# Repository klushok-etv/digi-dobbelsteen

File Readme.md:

# Digi Dobbelsteen

Digi Dobbelsteen is a digital dice project based on the attiny85 that uses 7 LEDs and a push button.

## Features

- 7 LEDs to display the result of the dice roll
- A push button to roll the dice
- A vibration sensor to roll the dice when the device is shaken

## Usage

The code was written in PlatformIO, so you can use that to compile and upload the code to the attiny85.

The schematic was made in KiCad 7.0, so you can use that to open the schematic and PCB files.

## Schematic

## Charlieplexing

## PCB

## Programing

A precompiled binary is available for the attiny13 under releases. Upload to the chip using the following command:

```console
avrdude -p attiny13 -c usbasp-clone -B 100kHz -e -U flash:w:t13dobbelsteen.elf -U lfuse:w:t13dobbelsteen.elf -U hfuse:w:t13dobbelsteen.elf -U eeprom:w:t13dobbelsteen.elf -U lock:w:t13dobbelsteen.elf
```

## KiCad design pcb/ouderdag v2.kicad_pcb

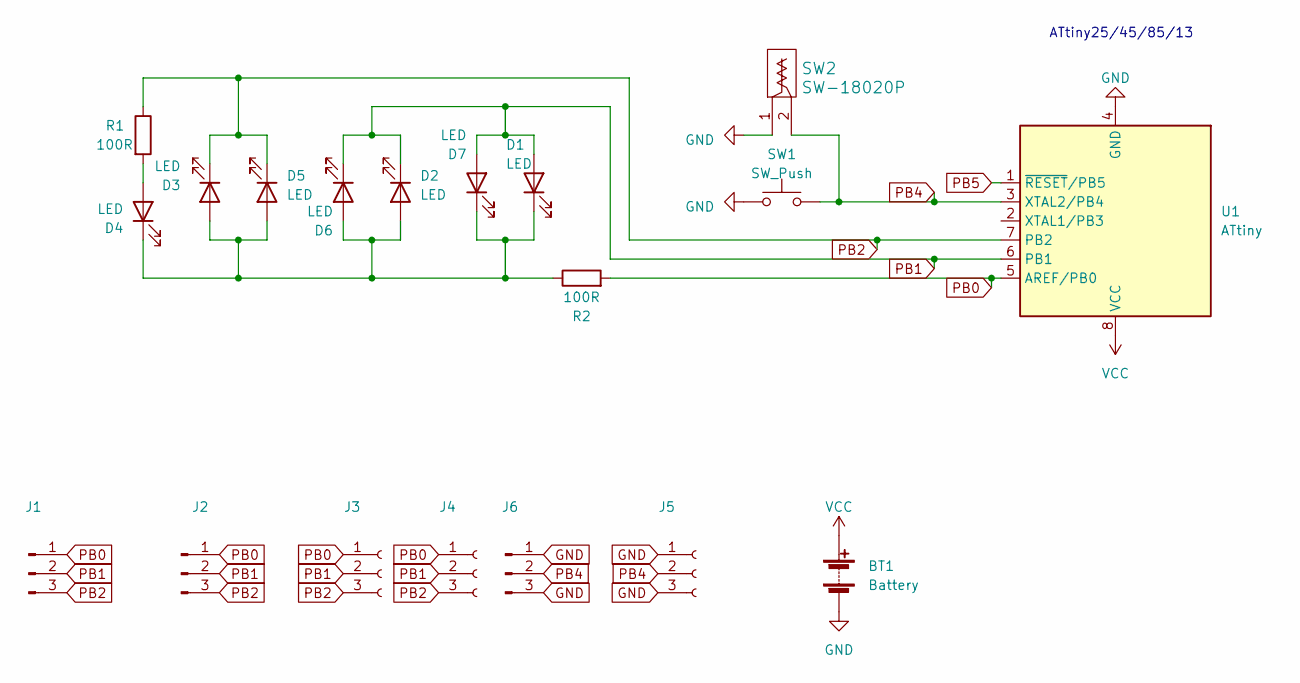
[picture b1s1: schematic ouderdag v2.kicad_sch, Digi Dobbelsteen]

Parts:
BT1: Battery; cr2032
D1, D2, D3, D4, D5, D6, D7: LED; LED_D10.0mm
J1, J2, J6: Conn_01x03_Pin; PinHeader_1x03_P2.54mm_Vertical
J3, J4, J5: Conn_01x03_Socket; PinSocket_1x03_P2.54mm_Vertical
R1, R2: 100R; R_Axial_DIN0207_L6.3mm_D2.5mm_P10.16mm_Horizontal
SW1: SW_Push; SW_PUSH-12mm
SW2: SW-18020P
U1: ATtiny; DIP-8_W7.62mm

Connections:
GND: BT1.2 (-), J5.1, J5.3, J6.1, J6.3, SW1.1, SW2.1, U1.4 (GND)
unnamed: D1.1 (K), D2.2 (A), D3.2 (A), D4.1 (K), D5.2 (A), D6.2 (A), D7.1 (K), R2.1
unnamed: D4.2 (A), R1.2
PB0: J1.1, J2.1, J3.1, J4.1, R2.2, U1.5 (AREF/PB0)
PB1: D1.2 (A), D2.1 (K), D6.1 (K), D7.2 (A), J1.2, J2.2, J3.2, J4.2, U1.6 (PB1)
PB2: D3.1 (K), D5.1 (K), J1.3, J2.3, J3.3, J4.3, R1.1, U1.7 (PB2)
PB4: J5.2, J6.2, SW1.2, SW2.2, U1.3 (XTAL2/PB4)
PB5: U1.1 (~RESET/PB5)
VCC: BT1.1 (+), U1.8 (VCC)

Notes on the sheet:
ATtiny25/45/85/13

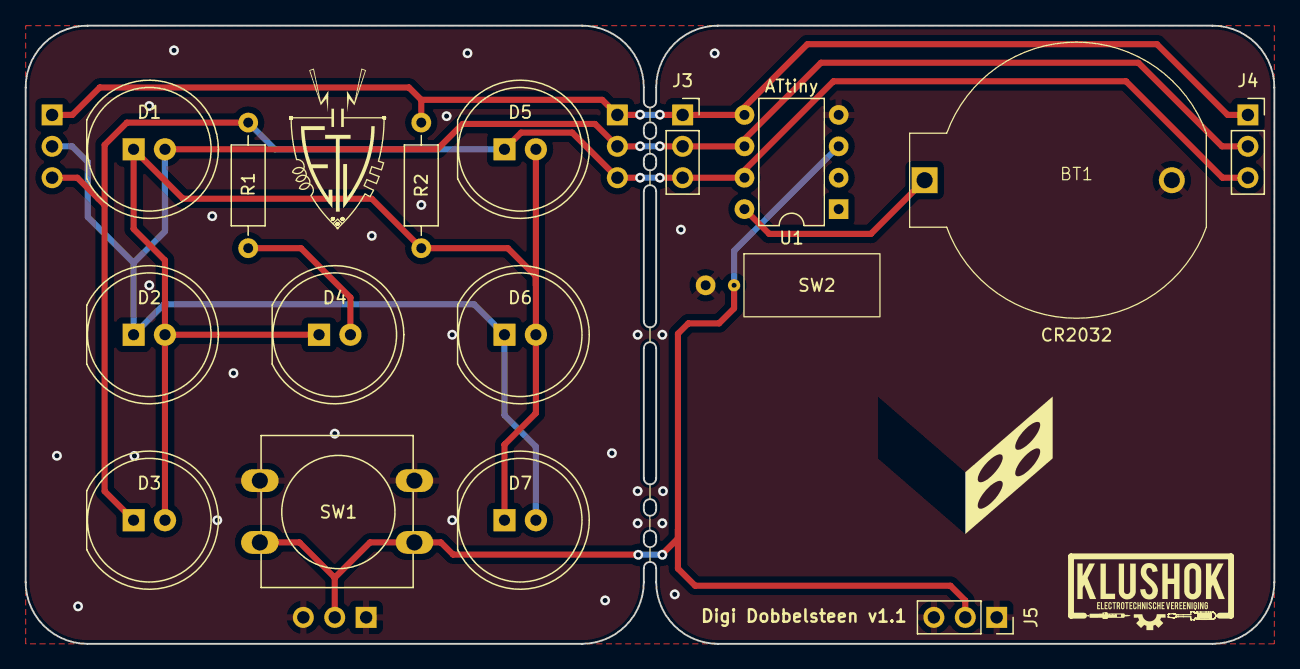
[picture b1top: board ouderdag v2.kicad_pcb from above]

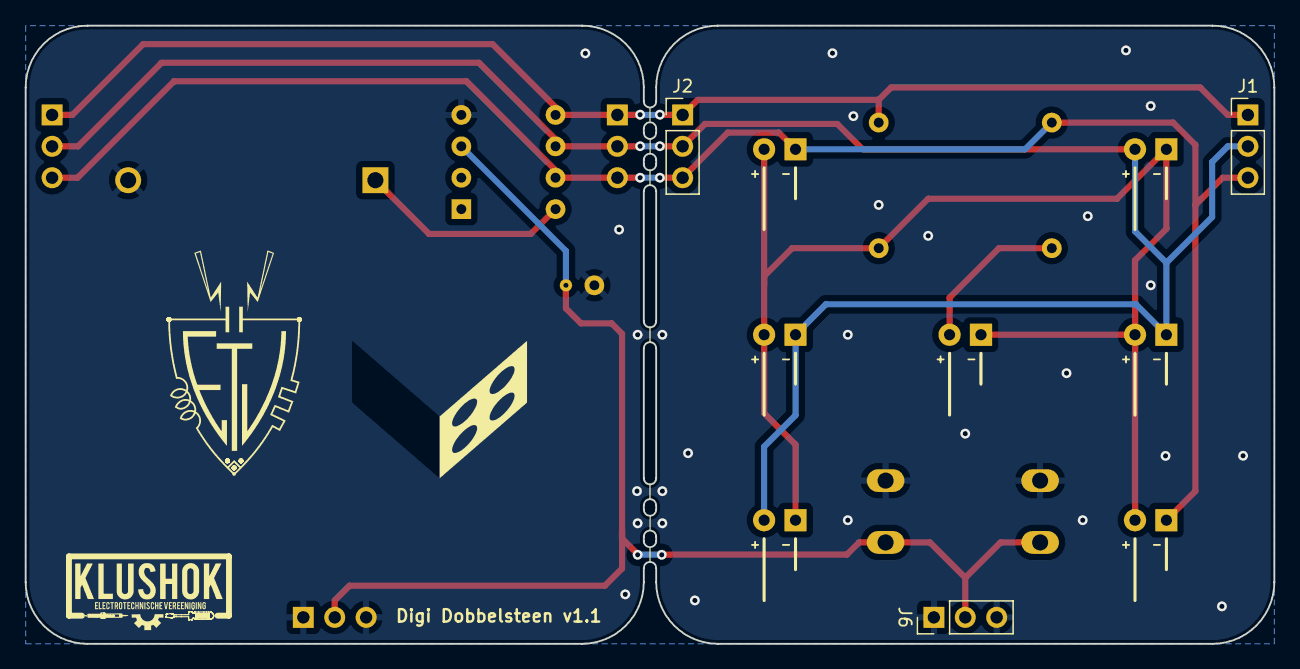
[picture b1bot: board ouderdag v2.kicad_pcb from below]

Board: 2 copper layers, 101.0 x 50.0 mm, 21 parts (4 on the bottom side), 8 nets.

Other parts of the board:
Ref**: Val**; Art
Ref**#2: Val**; Art

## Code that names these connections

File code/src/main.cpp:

/* Attiny Dice v1
  Ryan Kolk - Electrotechnische Vereeniging - 2024
  ATtiny85 @ 8 MHz (internal oscillator; BOD disabled)
   
  CC BY 4.0
  Licensed under a Creative Commons Attribution 4.0 International license: 
  http://creativecommons.org/licenses/by/4.0/

  Atmet Attiny 25/45/85 pinout
                   +-\/-+
  Ain0 (D 5) PB5  1|    |8  Vcc
  Ain3 (D 3) PB3  2|    |7  PB2 (D 2) Ain1
  Ain2 (D 4) PB4  3|    |6  PB1 (D 1) pwm1
             GND  4|    |5  PB0 (D 0) pwm0
                   +----+
*/

#include <Arduino.h>
#include <avr/sleep.h>    // Sleep Modes
#include <avr/power.h>    // Power management

void goToSleep ();

int animateRolling();
void nonBlockingDelay(int ms);
void flashNumber(int num);
void displayNumber(int num);
//Initial brightness levels for the rows
bool Level[4] = {0,0,0,0};
const uint8_t animation[4] = {1,2,3,2};

//Matrix to map numbers 1-6 to the correct leds
const bool Number[6][4] = {
  {1,0,0,0},
  {0,1,0,0},
  {1,1,0,0},
  {0,1,0,1},
  {1,1,0,1},
  {0,1,1,1},
};
bool interrupt = false;
bool awake = true;
static uint8_t row, ramp;
void(* resetFunc) (void) = 0;

ISR (PCINT0_vect)        // Interrupt service routine 
{
  MCUCR&=~(1<<SE);      //Disabling sleep mode inside interrupt routine
  if(awake && digitalRead(PB4) == LOW){
    // resetFunc();
    interrupt=true;
  }
}


// Timer overflow interrupt
ISR(TIM1_COMPA_vect) {
  static uint8_t dir, out;
    row = (row + 1) & 0x03;
    if(row == 0){
      dir=0b101;
      out=0b100;
    } else if(row == 1){
      dir=0b101;
      out=0b001;
    } else if(row == 2){
      dir=0b011;
      out=0b001;
    } else if(row == 3){
      dir=0b011;
      out=0b010;
    }
  if (Level[row] == 0){            // Turn off LED if brightness is 0
    out = 0b000;
    dir=0b000;
  }
  
  DDRB = (DDRB & 0xF8) | dir;         // Set Pin direction. 1 is output, 0 is input (High impedance)
  PORTB = (PORTB & 0xF8) | out;       // Set Pin. 1 is high, 0 is low
}

void setup() {
  if(F_CPU == 8000000) clock_prescale_set(clock_div_1); // Set clock to 8MHz

  // Set up Timer/Counter1 to contol the LEDs
  TCCR1 = 1<<CTC1 | 1<<CS10;          // Divide by 2
  GTCCR = 0;                          // No PWM
  OCR1A = 0;
  OCR1C = 125-1;                      // 16kHz
  TIMSK = TIMSK | 1<<OCIE1A;          // Compare Match A interrupt

  //Setup sleep with interrupt on PB4
  pinMode (PB4, INPUT);     
  digitalWrite (PB4, HIGH);           // Set internal pullup
  PCMSK  |= bit (PCINT4);             // interrupt on PB4
  GIFR   |= bit (PCIF);               // Clear any outstanding interrupts
  GIMSK  |= bit (PCIE);               // Enable pin change interrupts 
  GIMSK |= (1 << PCIE);
  int randomness = analogRead(PB3);// Get a bit of randomness from analog pin that is not being used
  randomSeed(randomness);    // Set seed for the random number generator
}
void loop () {
  int number = animateRolling();

  delay(300);
  flashNumber(number);
  interrupt=false;
  nonBlockingDelay(1500);
  if(interrupt){
    interrupt = false;
    return;
  }
  goToSleep();
  
}

int animateRolling(){
  int randomNumber = 0;
  int length = random(6,15);
  for(int i=0; i<length; i++){
    randomNumber = random(0,6);
    displayNumber(randomNumber);
    nonBlockingDelay(50 + (i * 350 / length));
    if(interrupt){
      length = random(6,15);
      i=0;
      interrupt = false;
      delay(50);
    }
  }
  return randomNumber;
}

void nonBlockingDelay(int ms) {
  for(int i=0; i<ms; i++){
    delay(1);
    if(interrupt)
     return;
  }
  return;
}

void flashNumber(int num){
  for(int i=0; i<2; i++){
    displayNumber(num);
    delay(400);

    displayNumber(-1);
    delay(400);
  }
  displayNumber(num);
}

void displayNumber(int num){
  if(num == -1){
    for(int i=0; i<4; i++){
      Level[i] = 0;
    }
  } else {
    for(int i=0; i<4; i++){
      Level[i] = Number[num][i];
    }
  }
  
}

void goToSleep () {
  for(int i=0; i<4; i++){
    Level[i] = 0;
  }
  MCUCR|=(1<<SM1);      // Enabling sleep mode and powerdown sleep mode
  MCUCR|= (1<<SE);     //Enabling sleep enable bit
  DDRB = (DDRB & 0xF8) | 0b000;
  PORTB = (PORTB & 0xF8) | 0b000;
  delay(10);
  ramp=0;
  row=0;
  awake = false;
  backtosleep: 
  set_sleep_mode(SLEEP_MODE_PWR_DOWN);
  ADCSRA = 0;                         // turn off ADC
  power_all_disable ();               // power off ADC, Timer 0 and 1, serial interface
  sleep_enable();
  sei();  
  sleep_cpu();   
  cli();                            
  sleep_disable();  
  sei();       
  power_all_enable();                 // power everything back on
  if(digitalRead(PB4) == HIGH){
    goto backtosleep;
  }
  awake = true;
}

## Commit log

2024-02-13 added start on manual
2024-03-22 updated code and pcb
2024-03-22 Update semiautomatic.sh
    Fix input queue issue
2024-03-23 cleanup repo
2025-03-27 change to generic ATtiny
    PCB changes:
    version 1.0 -> version 1.1
    ATtiny85 -> ATtiny
    mousebite trace FFF -> FBF
    removed order number
2026-02-12 add t13 code
2026-02-12 sleep function update
2026-02-25 Update Readme.md
    added upload command
